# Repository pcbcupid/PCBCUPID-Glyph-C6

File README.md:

# PCBCUPID-GLYPH-C6-PCB

This repo contains open source PCB files for PCBCUPID Glyph C6
This particular PCB is designed using Kicad v8.0

**This design has been built and tested successfully!**
For more details, check out the product pages at

   * [Glyph-C6](https://shop.pcbcupid.com/product/gd002/)

We are here to build India's largest open source hardware community, If you like to support
please consider buying the product from the above link!

[Creative Commons Attribution, Share-Alike license](https://creativecommons.org/licenses/by-sa/4.0/deed.en)
All text above must be included in any redistribution

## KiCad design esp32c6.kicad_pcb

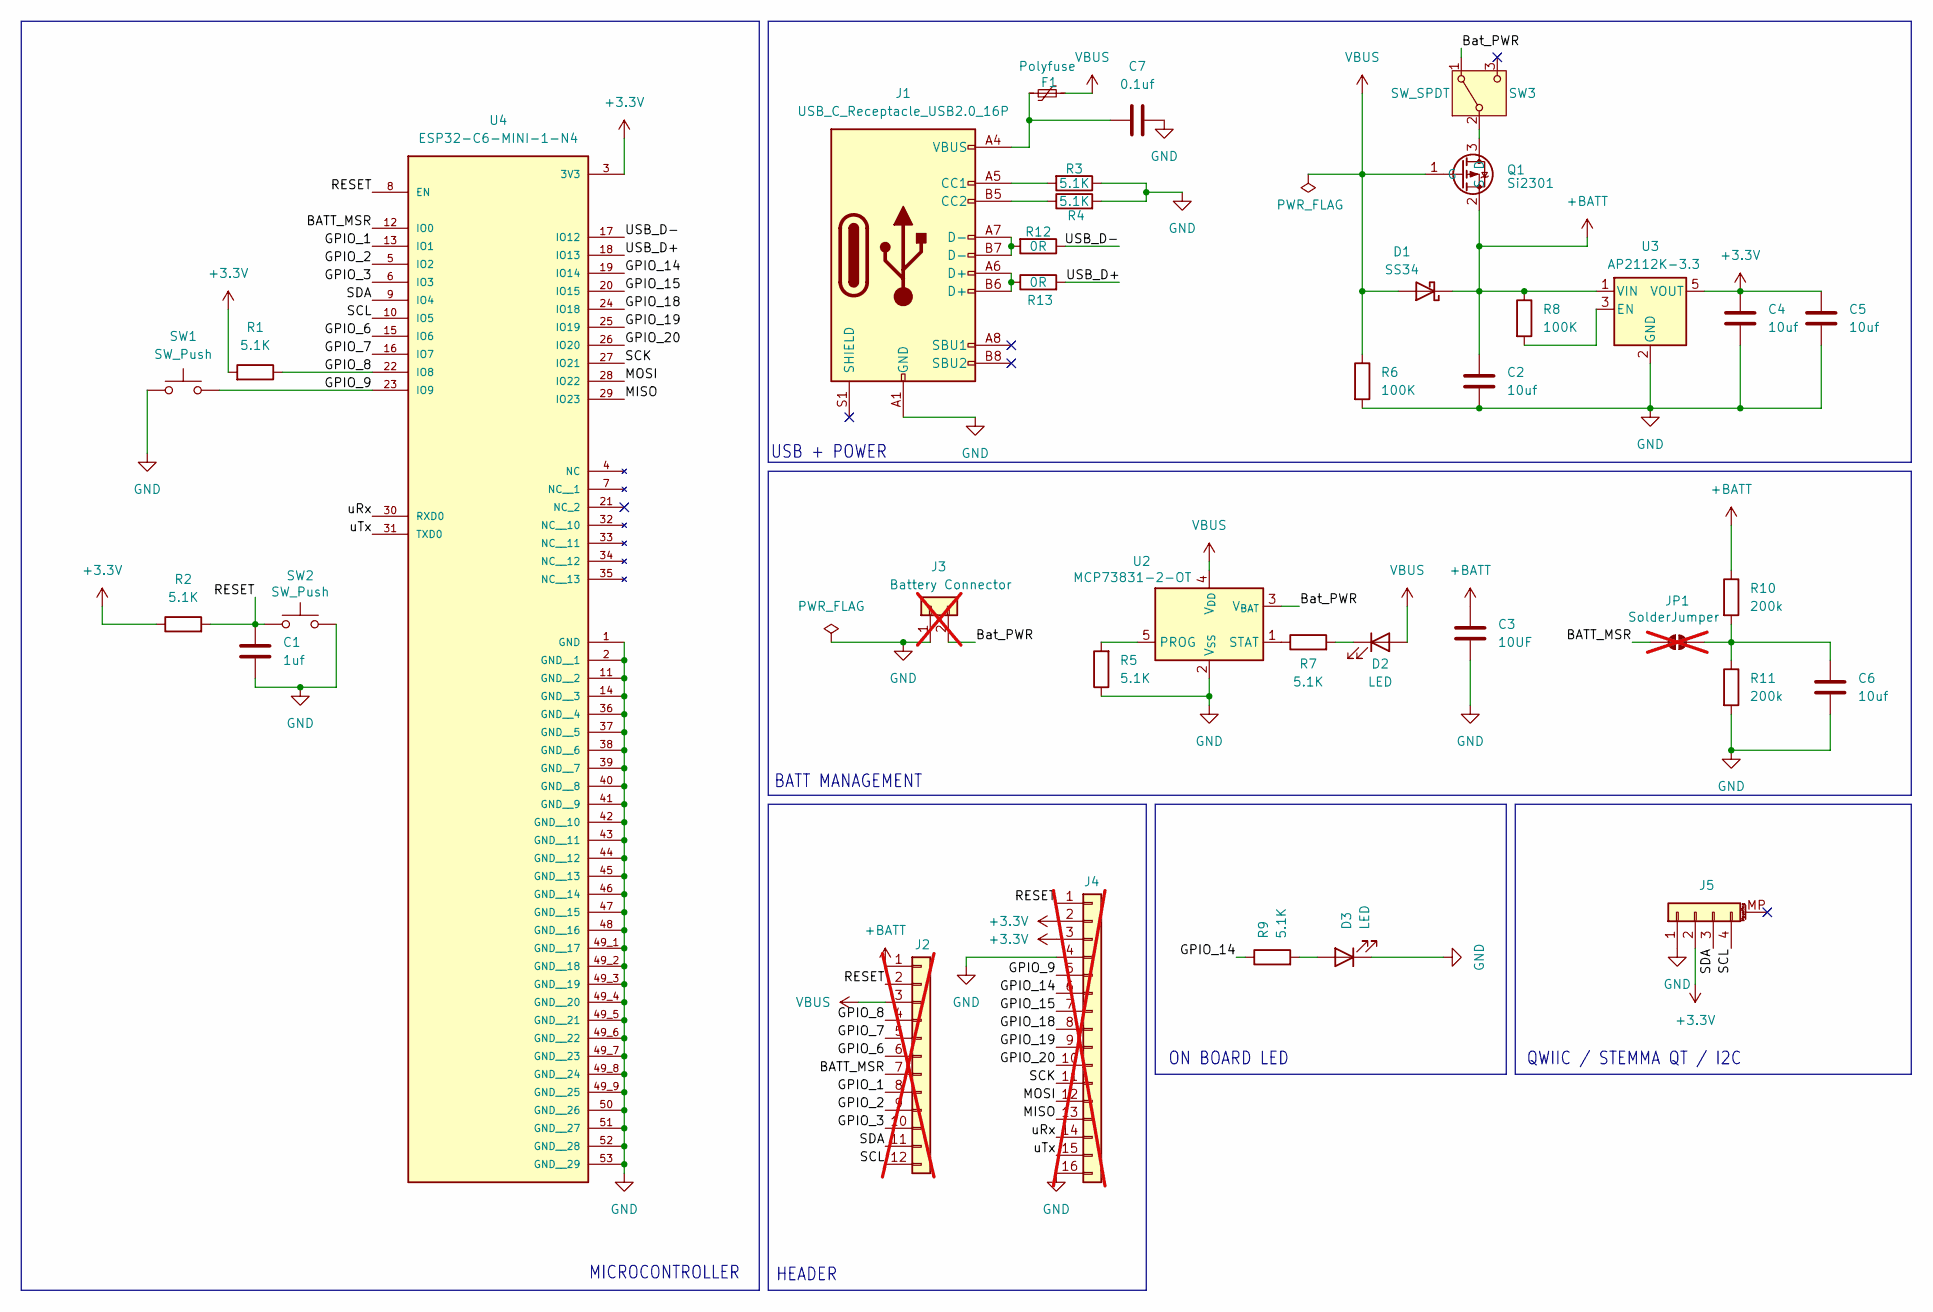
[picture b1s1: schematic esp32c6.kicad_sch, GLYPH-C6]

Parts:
C1: 1uf; C_0603_1608Metric
C2, C4, C5, C6: 10uf; C_0603_1608Metric
C3: 10UF; C_0603_1608Metric
C7: 0.1uf; C_0603_1608Metric
D1: SS34; D_SMA
D2, D3: LED; LED_0603_1608Metric
F1: Polyfuse; Fuse_0805_2012Metric
J1: USB_C_Receptacle_USB2.0_16P; USB_C_Receptacle_Palconn_UTC16-G
J2: Conn_01x12; PinSocket_1x12_P2.54mm_Vertical; not fitted
J3: Battery Connector; TestPoint_01x02; not fitted
J4: Conn_01x16; PinSocket_1x16_P2.54mm_Vertical; not fitted
J5: Conn_01x04_MountingPin; JST_SH_BM04B-SRSS-TB_1x04-1MP_P1.00mm_Vertical
JP1: SolderJumper; SolderJumper-2_P1.3mm_Open_RoundedPad1.0x1.5mm; not fitted
Q1: Si2301; SOT-23
R1, R2, R3, R4, R5, R7, R9: 5.1K; R_0603_1608Metric
R6, R8: 100K; R_0603_1608Metric
R10, R11: 200k; R_0603_1608Metric
R12, R13: 0R; R_0603_1608Metric
SW1, SW2: SW_Push; SW_SPST_PTS810
SW3: SW_SPDT; SW_SPDT_PCM12
U2: MCP73831-2-OT; SOT-23-5
U3: AP2112K-3.3; SOT-23-5
U4: ESP32-C6-MINI-1-N4; ESP32-C6-MINI-1_EXP; PARTREV v1.0

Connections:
+3.3V: C4.1, C5.1, J4.2, J4.3, J5.2, R1.2, R2.1, U3.5 (VOUT), U4.3 (3V3)
+BATT: C2.1, C3.1, D1.1 (K), J2.1, Q1.2 (S), R8.1, R10.1, U3.1 (VIN)
/BATT_MSR: J2.7, JP1.1 (A), U4.12 (IO0)
/Bat_PWR: J3.2, SW3.1 (A), U2.3 (V_{BAT})
/D+: J1.A6 (D+), J1.B6 (D+), R13.1
/D-: J1.A7 (D-), J1.B7 (D-), R12.2
/GPIO_1: J2.8, U4.13 (IO1)
/GPIO_2: J2.9, U4.5 (IO2)
/GPIO_3: J2.10, U4.6 (IO3)
/GPIO_6: J2.6, U4.15 (IO6)
/GPIO_7: J2.5, U4.16 (IO7)
/GPIO_8: J2.4, R1.1, U4.22 (IO8)
/GPIO_9: J4.5, SW1.1, U4.23 (IO9)
/GPIO_14: J4.6, R9.1, U4.19 (IO14)
/GPIO_15: J4.7, U4.20 (IO15)
/GPIO_18: J4.8, U4.24 (IO18)
/GPIO_19: J4.9, U4.25 (IO19)
/GPIO_20: J4.10, U4.26 (IO20)
/MISO: J4.13, U4.29 (IO23)
/MOSI: J4.12, U4.28 (IO22)
/RESET: C1.1, J2.2, J4.1, R2.2, SW2.1, U4.8 (EN)
/SCK: J4.11, U4.27 (IO21)
/SCL: J2.12, J5.4, U4.10 (IO5)
/SDA: J2.11, J5.3, U4.9 (IO4)
/USB_D+: R13.2, U4.18 (IO13)
/USB_D-: R12.1, U4.17 (IO12)
/uRx: J4.14, U4.30 (RXD0)
/uTx: J4.15, U4.31 (TXD0)
GND: C1.2, C2.2, C3.2, C4.2, C5.2, C6.2, C7.2, D3.1 (K), J1.A1 (GND), J1.A12 (GND), J1.B1 (GND), J1.B12 (GND), J3.1, J4.4, J4.16, J5.1, R3.1, R4.2, R5.1, R6.2, R11.2, SW1.2, SW2.2, U2.2 (V_{SS}), U3.2 (GND), U4.1 (GND), U4.2 (GND__1), U4.11 (GND__2), U4.14 (GND__3), U4.36 (GND__4), U4.37 (GND__5), U4.38 (GND__6), U4.39 (GND__7), U4.40 (GND__8), U4.41 (GND__9), U4.42 (GND__10), U4.43 (GND__11), U4.44 (GND__12), U4.45 (GND__13), U4.46 (GND__14), U4.47 (GND__15), U4.48 (GND__16), U4.49_1 (GND__17), U4.49_2 (GND__18), U4.49_3 (GND__19), U4.49_4 (GND__20), U4.49_5 (GND__21), U4.49_6 (GND__22), U4.49_7 (GND__23), U4.49_8 (GND__24), U4.49_9 (GND__25), U4.50 (GND__26), U4.51 (GND__27), U4.52 (GND__28), U4.53 (GND__29)
unnamed: C7.1, F1.1, J1.A4 (VBUS), J1.A9 (VBUS), J1.B4 (VBUS), J1.B9 (VBUS)
unnamed: D2.1 (K), R7.2
unnamed: D3.2 (A), R9.2
unnamed: J1.A5 (CC1), R3.2
unnamed: J1.B5 (CC2), R4.1
unnamed: C6.1, JP1.2 (B), R10.2, R11.1
unnamed: Q1.3 (D), SW3.2 (B)
unnamed: R5.2, U2.5 (PROG)
unnamed: R7.1, U2.1 (STAT)
unnamed: R8.2, U3.3 (EN)
VBUS: D1.2 (A), D2.2 (A), F1.2, J2.3, Q1.1 (G), R6.1, U2.4 (V_{DD})

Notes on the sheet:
ON BOARD LED
HEADER
BATT MANAGEMENT
QWIIC / STEMMA QT / I2C
MICROCONTROLLER
USB + POWER

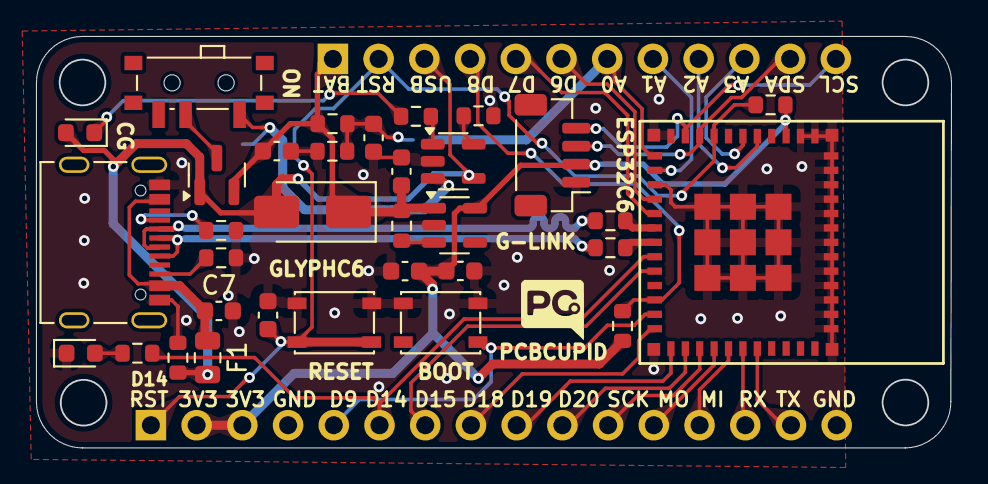
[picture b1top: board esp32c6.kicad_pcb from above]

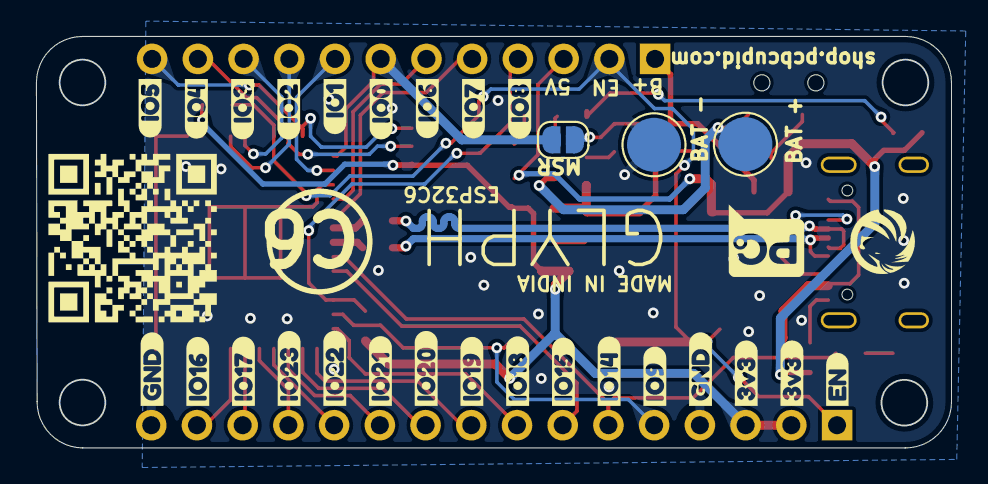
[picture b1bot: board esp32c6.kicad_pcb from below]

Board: 2 copper layers, 50.8 x 22.8 mm, 62 parts (28 on the bottom side), 40 nets.

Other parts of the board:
kibuzzard-668B7A7C: G***; kibuzzard-668B7A7C
kibuzzard-668B7A62, kibuzzard-668B7A62#2: G***; kibuzzard-668B7A62
kibuzzard-668B789B, kibuzzard-668B789B#2: G***; kibuzzard-668B789B
kibuzzard-668CCB9F: G***; kibuzzard-668CCB9F
kibuzzard-668CCB83: G***; kibuzzard-668CCB83
kibuzzard-668D15B0: G***; kibuzzard-668D15B0
kibuzzard-668D15B6: G***; kibuzzard-668D15B6
kibuzzard-668D15C1: G***; kibuzzard-668D15C1
kibuzzard-668D15F0: G***; kibuzzard-668D15F0
kibuzzard-668D15F7: G***; kibuzzard-668D15F7
kibuzzard-668D16B5: G***; kibuzzard-668D16B5
kibuzzard-668D17D0: G***; kibuzzard-668D17D0
kibuzzard-668D17D6: G***; kibuzzard-668D17D6
kibuzzard-668D170D: G***; kibuzzard-668D170D
kibuzzard-668D171B: G***; kibuzzard-668D171B
kibuzzard-668D175C: G***; kibuzzard-668D175C
kibuzzard-668D176A: G***; kibuzzard-668D176A
kibuzzard-668D1619: G***; kibuzzard-668D1619
kibuzzard-668D1621: G***; kibuzzard-668D1621
kibuzzard-668D1715: G***; kibuzzard-668D1715
kibuzzard-668D1721: G***; kibuzzard-668D1721
kibuzzard-668D1727: G***; kibuzzard-668D1727
kibuzzard-668D1756: G***; kibuzzard-668D1756

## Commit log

2024-09-05 Release v1.0.0
2025-06-18 Update README.md
    Changed C3 to C6 in description

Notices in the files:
esp32c6.kicad_sch:
License : CC-BY-SA
